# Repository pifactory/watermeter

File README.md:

# Smart Water Meter Sensor
 [![CC BY 4.0][cc-by-shield]][cc-by]

Design files for making inductive sensor for reading out smart water meters.

## Features

* 20 &mu;A in low-power mode (including microcontroller)
* Small footprint: 18mm x 32.5 mm, can be placed directly on the water meter glass
* Easy to use: inductive sensors are printed directly on the PCB
* Designed for wheel diameter of 18mm
* Includes 2 inductive sensors for reliable counting of the wheel turns

## How Smart Water Meter works

Many water meters are made 'smart-ready', ie they include a wheel under the glass
which makes 1 turn per liter. Half of the wheel contains some metal (copper) on it
which can be sensed by an inductive sensor.

Because of the costs water supply companies usually do not install smart reading device
on such meters, but some nerds among us are stubborn enough to design and install
their own reading device. Just to know how much water is used and be able to monitor it
with, say, a Home Assistant. It can be also used to detect leaks.

One inductive sensor is not enough for reliable readings. There are some corner
cases when the sensor will miss a turn of the wheel or count 1 turn 2 times. Think of it like
this: wheel can stop at any moment at any angle and then continue movement at any
time later on. During this stop environment can change significantly (temperature &
humidity) to fool the sensing circuit. On top of it, to save power, each inductive
sensor is scanned once in 800ms, ie there is no continous output from it. All in all,
2 inductive sensors allow to detect illogical readings and in many cases repair them.

For now here is just the sensor, controller is coming soon... I've made one for
Zigbee already and it runs on 2 AAA batteries.

Here is the photo of the first prototype:

## How to use design files

I used KiCAD 6 to make the design. You will probably also want to install [kicad-goodies](https://github.com/pifactory/kicad-goodies) libraries, but this is not required.

A word about choosing a PCB shop. Inductive sensors on the PCB require as much as possible turns
on as little space possible. This means that the traces have to be as thin as possible and the
spacing between them has to be as small as possible. Also there is no copper around them +
geometry of the traces = you might get shorts between traces if you push it to the limit.

Most shops out there (including JLCPCB) claim to be able to produce 6 mils traces with 6 mils spacing
between them. I work with AISLER and they produce 5/5 mils boards for the same price,
so this design has 5/5 PCB coils. I've made 6/6 PCB coils available in 
[kicad-goodies](https://github.com/pifactory/kicad-goodies), you can try them if 5/5
coils will not work for you. AISLER will need just *.kicad_pcb file, no Gerber is needed there and therefore not provided in this repo.

## Zigbee Microcontroller

This repo has all you need to make a Zigbee microcontroller for the sensor:

* KiCAD 6 design files for the PCB (incl schematic)
* Compiled firmware
* Configuration file for Zigbee2MQTT

Microcontroller is based on EBYTE module with CC2652P.  

Firmware has following features:

* Low power, should work for years on 2 AAA batteries
* Water usage data is buffered for 5 minutes
* When parent connection is lost: try to rejoin every 5 minutes
* Transmit power is set to 14dBm, this should be enough to get signal in challenging RF situations and yet to not use too much battery

Because of a bug in TI software, rejoin period cannot be longer than 5 minutes. Also rejoin uses more power than standard data report, so try to avoid situations when device stays on for longer periods without a connection to the network (like days, weeks, months)

Operation with 2 buttons and 1 LED:
* Join new network: click BTN1
* Leave network: press BTN1 for at least 10 seconds and release the button (long click)
* Immediately send data (when part of the network): click BTN1
* Rejoin (when parent is lost): click BTN1
* RESET button restarts the device
* LED blink once device (re-)joins Zigbee network

### Zigbee2MQTT

Place provided `pifactory_watermeter.js` file in the same directory as `configuration.yaml` file.

Add these lines to `configuration.yaml` file:

```yaml
external_converters:
    pifactory_watermeter.js
```

Restart Zigbee2MQTT and join the device

## Holder

I've made a holder which fits my Elster water meter. Meter without sensor looks like this:

I didn't tried the holder on any other meter, but I suspect it fits different models as well. Please share your meters/holders or contact me if you need help fitting this sensor to your meter.

---
This work is licensed under a
[Creative Commons Attribution 4.0 International License][cc-by].

[![CC BY 4.0][cc-by-image]][cc-by]

[cc-by]: http://creativecommons.org/licenses/by/4.0/
[cc-by-image]: https://i.creativecommons.org/l/by/4.0/88x31.png
[cc-by-shield]: https://img.shields.io/badge/License-CC%20BY%204.0-lightgrey.svg

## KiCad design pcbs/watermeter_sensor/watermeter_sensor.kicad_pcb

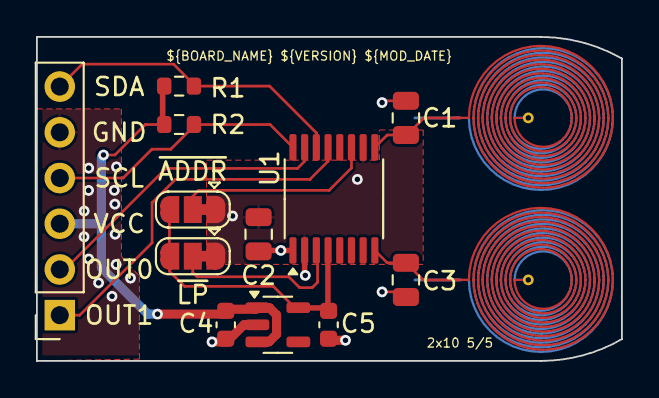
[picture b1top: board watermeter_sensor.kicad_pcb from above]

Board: 2 copper layers, 32.5 x 18.0 mm, 14 parts (0 on the bottom side), 12 nets.

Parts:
C1, C3: 1nF; C_0805_2012Metric
C2: 10nF; C_0805_2012Metric
C4, C5: 1uF; C_0603_1608Metric
J1: Conn_01x06; PinSocket_1x06_P2.54mm_Vertical
JP1: ~{ADDR}; SolderJumper-3_P1.3mm_Bridged12_RoundedPad1.0x1.5mm
JP2: ~{LP}; SolderJumper-3_P1.3mm_Bridged12_RoundedPad1.0x1.5mm
PXI1, PXI2: PCB coil; pcb_coil_8mm_2Lx10T_5-5
R1, R2: 30k; R_0603_1608Metric
U1: LDC2112; TSSOP-16_4.4x5mm_P0.65mm
U2: AP7354-18W5; TSOT-23-5

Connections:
+1V8: C5.1, JP1.3 (B), JP2.3 (B), U1.4 (VDD), U2.5 (VOUT)
/ADDR: JP1.2 (C), U1.11 (ADDR)
/COM: C1.2, C2.1, C3.2, PXI1.1, PXI2.1, U1.1 (COM)
/IN0: C1.1, PXI1.2, U1.9 (IN0)
/IN1: C3.1, PXI2.2, U1.8 (IN1)
/LPWRB: JP2.2 (C), U1.3 (LPWRB)
/OUT0: J1.2, U1.15 (OUT0)
/OUT1: J1.1, U1.13 (OUT1)
/SCL: J1.4, R2.2, U1.16 (SCL)
/SDA: J1.6, R1.2, U1.14 (SDA)
GND: C2.2, C4.2, C5.2, J1.5, JP1.1 (A), JP2.1 (A), U1.2 (GND), U1.10 (GND), U2.2 (GND)
VCC: C4.1, J1.3, R1.1, R2.1, U2.1 (VIN), U2.3 (EN)

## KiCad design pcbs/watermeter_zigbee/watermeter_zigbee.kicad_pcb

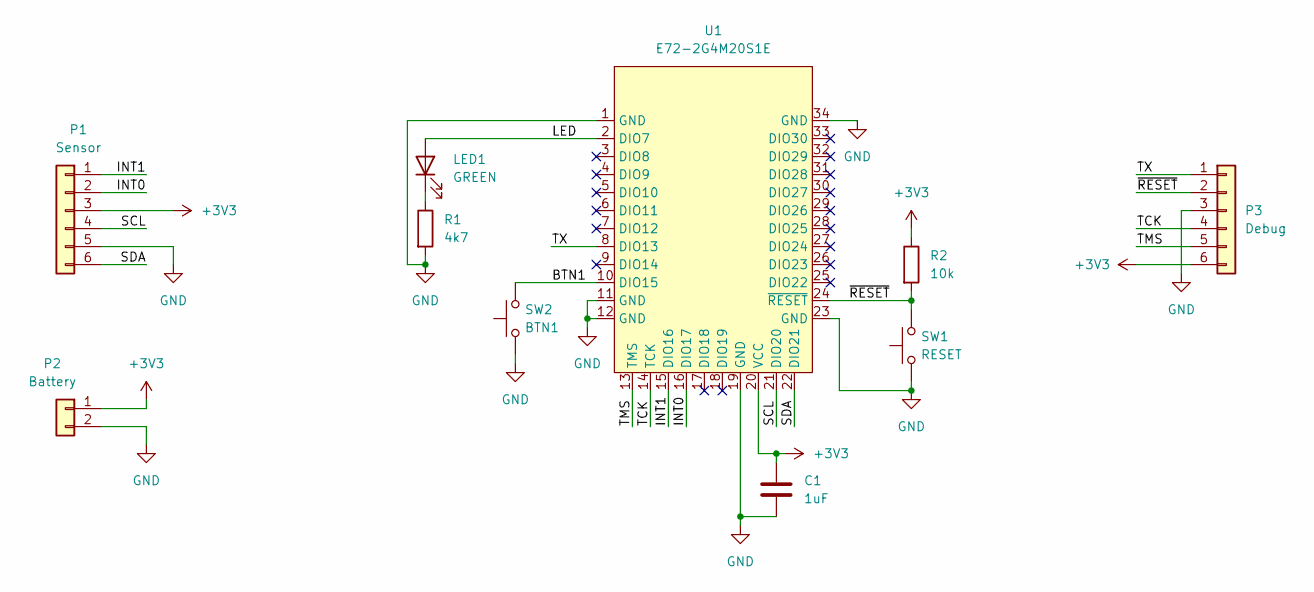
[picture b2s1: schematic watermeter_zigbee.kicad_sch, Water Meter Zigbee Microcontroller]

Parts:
C1: 1uF; C_0402_1005Metric
LED1: GREEN; LED_1206_3216Metric
P1: Sensor; PinHeader_1x06_P2.54mm_Vertical
P2: Battery; BatteryHolder_Keystone_2468_2xAAA
P3: Debug; PinHeader_1x06_P2.54mm_Vertical
R1: 4k7; R_0805_2012Metric
R2: 10k; R_0805_2012Metric
SW1: RESET; SW_SPST_EVQP2
SW2: BTN1; SW_SPST_EVQP2
U1: E72-2G4M20S1E

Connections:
+3V3: C1.1, P1.3, P2.1, P3.6, R2.1, U1.20 (VCC)
/BTN1: SW2.2, U1.10 (DIO15)
/INT0: P1.2, U1.16 (DIO17)
/INT1: P1.1, U1.15 (DIO16)
/LED: LED1.2 (A), U1.2 (DIO7)
/SCL: P1.4, U1.21 (DIO20)
/SDA: P1.6, U1.22 (DIO21)
/TCK: P3.4, U1.14 (TCK)
/TMS: P3.5, U1.13 (TMS)
/TX: P3.1, U1.8 (DIO13)
/~RESET: P3.2, R2.2, SW1.2, U1.24 (~RESET)
GND: C1.2, P1.5, P2.2, P3.3, R1.2, SW1.1, SW2.1, U1.1 (GND), U1.11 (GND), U1.12 (GND), U1.19 (GND), U1.23 (GND), U1.34 (GND)
unnamed: LED1.1 (K), R1.1

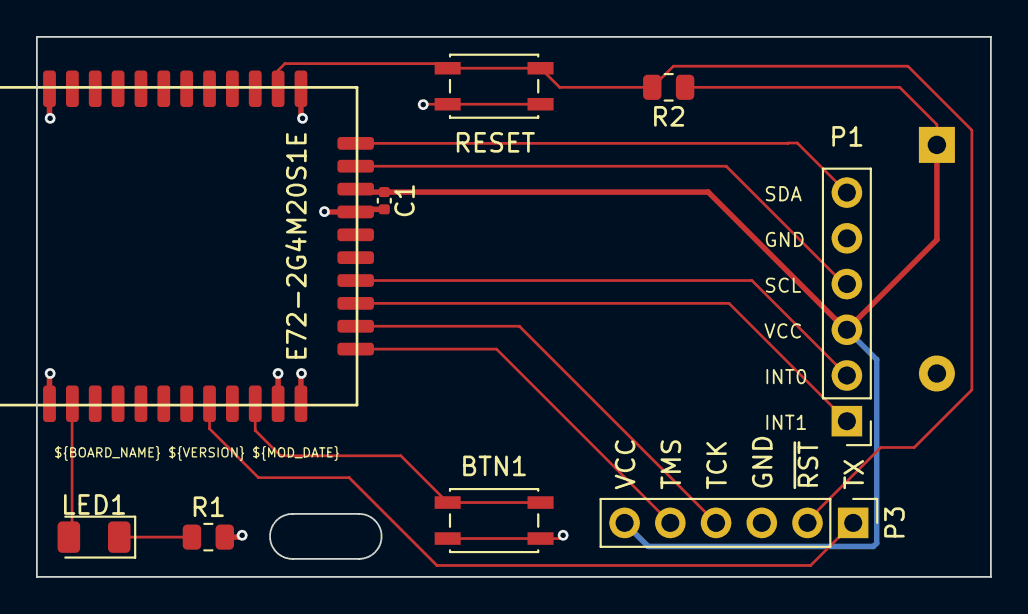
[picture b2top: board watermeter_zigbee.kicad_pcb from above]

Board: 2 copper layers, 53.0 x 30.0 mm, 10 parts (1 on the bottom side), 13 nets.

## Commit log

2021-11-14 Add Zigbee Microcontroller design files
2022-04-30 Add Arduino example
2022-04-30 Add tindie badge
2024-08-07 chore: Update .gitignore, upgrade to KiCAD 8
2024-08-07 PCB Changes v1.1: - changed LDO - some footprints changed to 0603
2024-08-08 Update design rules to latest AISLER HD Boards
2024-08-08 chores
2024-08-09 minor tweaks
2024-09-14 Update Arduino library
2024-09-14 Watermeter v1.1 (#6)
    * Update Arduino library
    * PCB Changes v1.1:
    - changed LDO
    - some footprints changed to 0603

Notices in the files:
pcbs/watermeter_zigbee/watermeter_zigbee.kicad_sch:
Copyright (c) 2021 Alexander Dvorkovyy
